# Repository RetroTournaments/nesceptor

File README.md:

# NESceptor

The NESceptor is a small hardware mod that adds a USB output to a 1985 Nintendo Entertainment System.
This mod is designed to provide support for speedrunning and speedrunning competitions.
The primary use case is to:

 - Allow for live RAM watch
 - Transmit console power status
 - Transmit precise timing information

## Design Decisions

### Why this overall design?

The console is to be treated with respect.
Although nearly [62 million units](https://en.wikipedia.org/wiki/Nintendo_Entertainment_System) were sold, they are no longer manufactured and should not be unnecessarily damaged.
The case (shell) of the Nintendo Entertainment system is _not_ to be cut or irreversibly modified.
The electronics are _not_ to be irreversibly modified.

To satisfy this requirement - while also balancing the desires to be able to quickly install a NESceptor - a two-part design was chosen.
The first board sits inside the console and attaches directly to the back of the CPU via a series of castellations.
This first board provides level translation and hosts the microcontroller which does all necessary i/o and processing.

The second part sits in the small outside slot on the back of the console and is attached via double sided tape and a small cable which goes back to the in console pcb.
This second board has ESD protection and the USB port for power in and data trasmission out.

A rough block diagram is below:

```
                     +--inconsole/--------------------+   +--usbport/---------+
     +------------+  |  +--------+    +------------+  |   |                   |
     |            |  |  |        |    |            |  |   | USB connection    |
     | NES CPU    |  |  | 5V to  |    | Rp2350     |  |   |                   |
     |            |  |  | 3.3V   |    | Micro-     |  |   | ESD protection    |
     | 8 data     |  |  |        |    | controller |  |   |                   |
     | 14 addr    | --> | Level  | -> |            | ---> |                   |
     | 3 aux      |  |  | Trans- |    | Watching / | <--- |                   |
     | --         |  |  | lators |    | Filtering  |  |   |                   |
     | 25 signals |  |  |        |    |            |  |   |                   |
     |            |  |  |        |    |            |  |   |                   |
     +------------+  |  +--------+    +------------+  |   |                   |
                     +--------------------------------+   +-------------------+ 
```

### Why Castellations?

The `inconsole` pcb is connected to the NES CPU with 40 castellations.
Consider:

- Removing the CPU and/or PPU can be difficult for novices (ahem) and requires patience, dedicated tools, and practice.
  Then once removed a socket is installed, and the CPU/PPU have to be installed into yet another socket, and the whole thing is fiddly and may lead to damage.
- The CPU itself is not subjected to heat or potential damage (when removing it), and is left basically alone with this design.
- A flex pcb was tried at one point, but it proved very difficult to install and remove.
  Flex pcbs are also more expensive to manufacture.

The main drawback to the castellations is that they may make the nesceptor difficult to remove, although this has not been tested yet.

### Which signals are needed from the console?

The following signals are absolutely required:

- Data lines 0 to 7 (8 total), these are self explanatory!
- Address lines 0 to 10 and 13-15 (14 total). Address lines 11 and 12 are not necessary because they are [unmapped](https://www.nesdev.org/wiki/CPU_memory_map).
- `NES_RST` when low the console is off, and that is important to know.
- `M2` is the clock
- `R/W` for read / write (low is write) 

This gives a total of 25 signals.

Historically `NMI` was also watched - but it was not used in the first version.
Maybe the controller pins are important, or `IRQ`, but they were never hooked up in the original.

### Notes on level translation

The NES is a 5V system, which is relatively high by modern standards, as most modern microcontrollers only have 3.3V tolerant inputs.
For example the [RP2350 datasheet](https://datasheets.raspberrypi.com/rp2350/rp2350-datasheet.pdf) indicates a maximum 3.63V supply voltage (`IOVDD`) and `IOVDD + 0.3` as maximum input voltage.
The NES signals must be translated to not damage the microcontrollers.

The level translators must not be used to change or interact with the console whatsoever.
They are preferably unidirectional.
This is imperative to maintain the legitimacy of the speedrunning and should be easily verified by third parties.

### Why the RP2350?

An earlier version of the NESceptor used an FPGA - specifically the Lattice iCE40 HX on the Alchitry CU development board, however:

- FPGAs are expensive.
- FPGAs are difficult to program (requiring some HDL).

The RP2350 is cheaper and should be capable of reading the NESs roughly 2 MHz signals:

- [This logic analyzer project](https://github.com/gusmanb/logicanalyzer/tree/master) uses a raspberry pi pico and boasts 100Msps
- And [this one](https://github.com/dotcypress/ula) also gets similar speeds.

### Why USB

USB is simple and well supported, people probably already have a ton of cables.
This will allow for communication and power delivery.
Ethernet is not necessary in this application because the nesbox mini pc will handle that, and would introduce some additional complications when it comes to networking.
Wifi for communication is expected to be unreliable - although this is unknown.

## Dev Instructions

### PCB Development

Install [KiCad](https://www.kicad.org/) for schematics / pcb design / etc.
I just use `snap install kicad`.
This got me `kicad 9.0.1` last time.
I'm using KiCad because it's free, and this is an open source project.

### Enclosure Development

Install [OpenSCAD](https://openscad.org/) for the 3d printed usbport enclosure.
I just use `snap install openscad`.
This got me `openscad 2021.01` last time.
I'm using OpenSCAD because its free, programmatic, and this is an open source project.

### Firmware Development

Firmware is developed using the [RP2350 C/C++ SDK](https://www.raspberrypi.com/documentation/microcontrollers/c_sdk.html).

To get started you need to have cloned this repo with submodules, or else use `git submodule update --init --recursive`.
Install the necessary prerequisites for the pico sdk:

```
sudo apt install cmake gcc-arm-none-eabi libnewlib-arm-none-eabi libstdc++-arm-none-eabi-newlib
```

Then you have to initialize the cmake build system with:

```
mkdir build
cd build
../scripts/cmake.sh
```

Then to build the firmware (source code in `include/` and `src/`), simply use `make`.

To flash the firmware to the nesceptor you need to hold the bootsel button when plugging it in, and then drag and rop the completed `.uf2` file onto the device.
It should then reboot and start running immediately.

### Ordering instructions

Under construction.

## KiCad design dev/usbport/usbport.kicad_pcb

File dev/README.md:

# Dev log

## 2025-10 `testbench/` Design

Round two developing nesceptor begins.
New thoughts:

  - Document more of the development process / decisions.
  - Order everything with PCB assembly.
    I am sick of debugging soldering issues.
    I also want to be able to order more easily - and not have to spend assembly time on my side.

Today I verified that my little TXU0104PWR breakout board worked.
Also, my original connector Molex 5051104091 is on the JLCPCB Parts library!

First item to design / order is a 5051104091 -> Digital discovery adapter that allows for exploration of the signals, and allows hooking up the pico 2 for initial development.
A sort of test bench hence the directory: `testbench/`.

- 5051104091, connector to get all 40 signals from the CPU
- To 5v -> 3.3v level translater prototype
    - TLV1117LV33DCYR for 5v to 3.3v (first test for this part)
    - TXU0104 translators (second implementation of this part)
- To pins with labels (all pins!?)

Review of the connector from my current breakout installed in several NESes

```
5051104091
                    |    |
                    |    |
              40            --  +5V
              39            ->  OUT0
              38            ->  OUT1
------------  37            ->  OUT2 
              36            ->  /OE1  
              35            ->  /OE2  
              34            ->  R/W   
              33            <-  /NMI  
              32            <-  /IRQ
              31            ->  M2
              30            <-  TST (usually GND)
              29            <-  CLK
              28            <>  D0
              27            <>  D1
              26            <>  D2 
              25            <>  D3 
              24            <>  D4 
              23            <>  D5 
              22            <>  D6
              21            <>  D7
 cable        20            --  GND
              19            ->  A15
              18            ->  A14 
              17            ->  A13  
              16            ->  A12   
              15            ->  A11    
              14            ->  A10     
              13            ->  A9      
              12            ->  A8       
              11            ->  A7        
              10            ->  A6         
               9            ->  A5          
               8            ->  A4           
               7            ->  A3            
               6            ->  A2             
               5            ->  A1              
------------   4            ->  A0               
               3            <-  RST
               2            ->  AD2
               1            ->  AD1
                    |    |
                    |    |
```

The rev 1 testbench has a little section for converting the NES 5v to 3.3v, and then some translators to get the signals into the digital discovery.
I ordered it, now to wait for it to show up.

The plan for when it does is to hook it up to the nes and the [Digital Discovery](https://digilent.com/shop/digital-discovery-portable-usb-logic-analyzer-and-digital-pattern-generator/).
This will allow me to document some of the timing information I will need when developing the inconsole firmware.
I have some earlier things kicking around - but they are not in keeping with the new repo structure and philosophy with documenting everything better.

## 2025-10 `inconsole/` -- rev 0

The next pcb I have designed and ordered is a 0th revision for the inconsole.
This is to see if I can fit all the parts, if I can design and order a working RP2350 board, and many other things.

Basically just following the RP2350 hardware design document, and shooting by the hip.
Going to try the RP2354A so I don't have to worry about fitting the flash on there.
I made an initial board which has all the level translation / power stuff contained within the necessary footprint of the NES CPU, and then some extra stuff on the outside for debugging and testing.
I ordered five of these with assembly and will try to learn as many lessons as possible from this.

First few things before it has even shown up.

- Sticking to 0402 components is helpful for assembly and keeping assembly costs down.
  I did 0201 for a bit, but then it was going to require more advanced assembly and higher costs.
- Ensure hole sizes are in tolerance.
- Include the pin 0 on silkscreen to avoid back and forth email.

Waiting for it to show up, and then will test!

## 2025-10 `usbport/` -- rev 0

Before even the other two revision 0s have shown up I'm investigating the `usbport/`.
Essentially I'm just going to steal the design from the [Unified Daughterboard](https://github.com/Unified-Daughterboard/UDB-S) project - which is another open source project primarily for mechanical keyboards.
Unfortunately their original design does not fit exactly where I want this to fit, so I will have to move things around a little bit probably screwing things up in the process.

One other main consideration about the usbport is that it needs a little enclosure to keep everything neat and tidy and protected.
I was originally thinking of coming out the left of the console - but we have power out the back, and composite out the right, so would be better to not add another cable out another side.
Then I ordered a unified daughterboard just to test, and the Pico EZMate connector is so small that it fits out the expansion port directly, and does not need to come out the vents.
Going to try for out the back on the 0th revision.

The back slot is about 99mm long, 12.5mm deep, ~16 mm wide (15.9 at 'top', 16.5 at 'bottom').
Let's imagine then 1.5mm thick walls on both sides, gives me a 12 mm wide pcb, 1.6mm thick.
I do not think I need to go the full length, but it would make it a bit easier for pushing the usb cable in to have some backing.
Regardless the PCB itself does not need to go to the back.

In keeping with stealing from the unified daughterboard project, we'll be using this [usb c connector - C165948](https://jlcpcb.com/partdetail/Korean_HropartsElec-TYPE_C_31_M12/C165948).

For the enclosure thinking of starting with a single hole in the middle M3 with [threaded inserts](https://www.mcmaster.com/products/threaded-inserts/threaded-inserts-3~/tapered-heat-set-inserts-for-plastic-7/).

## 2025-10 `inconsole/` -- rev 0 continued

The inconsole prototype showed up first and incredibly the RP2354a is actually working??
Just straight up plugged in the usb via a unified daughterboard (because my usbport rev is not done), and it just booted up with no problems..
Then I was able to install my own firmware - just a hello world thing, and it worked? Like uhhhhh. Insane!

> Rev 1 - Include the bootsel button within the final design. Actually no, the boot at 1200 baud does it.
> Rev 1 - Have not needed the run button or the debug port yet.

Now I need to test the 5V level translation part, and actually read the GPIO.
I wrote a small program (in this commit), and then just by shorting the RST pin to 5V with a little jumper cable it works.
No smoke either.
I just think everything is working?
We do have to get into the nitty gritty with timing and stuff now.
Hopefully testbench shows up - do I need to do some PIO stuff here?

## 2025-10 Wires
I ordered 200 25cm wires from [here](https://www.alibaba.com/product-detail/Customized-Molex-EZmate-78171-78172-1_1600697379284.html).
Hopefully long enough, and correct!

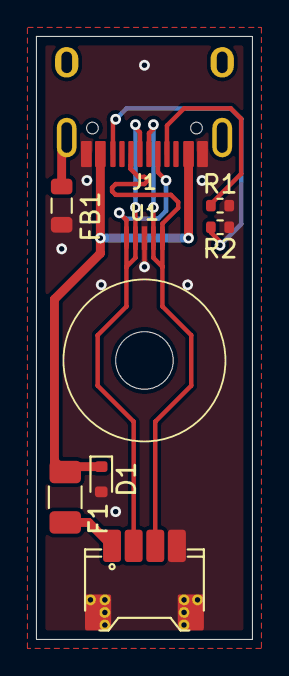
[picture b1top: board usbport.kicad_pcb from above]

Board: 2 copper layers, 12.0 x 33.5 mm, 9 parts (0 on the bottom side), 8 nets.

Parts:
D1: ESD5Z5V0; D_SOD-523
F1: SMD0805-050-16V; Fuse_1206_3216Metric
FB1: GZ2012D601TF; L_0805_2012Metric
H1: MountingHole; MountingHole_3.2mm_M3
J1: USB_C_Receptacle_USB2.0_16P; HRO-TYPE-C-31-M-12-Assembly
J2: Conn_01x04_MountingPin; PicoEZMate-Reinforced-Lite
R1, R2: 5.1k; R_0402_1005Metric
U1: TPD4E05U06DQAR; USON-10_2.5x1.0mm_P0.5mm

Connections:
+5V: F1.2, J2.1
D+: J1.A6 (D+), J1.B6 (D+), J2.3, U1.4 (D2+), U1.5 (D2-), U1.6 (NC), U1.7 (NC)
D-: J1.A7 (D-), J1.B7 (D-), J2.2, U1.1 (IO1), U1.2 (IO2), U1.9 (NC), U1.10 (NC)
GND: D1.2 (A2), FB1.2, J1.A1 (GND), J1.B1 (GND), J2.4, J2.MP (MountPin), R1.1, R2.2, U1.3 (GND), U1.8 (GND)
GNDPWR: FB1.1, J1.S1 (SHIELD)
unnamed: J1.A5 (CC1), R1.2
unnamed: J1.B5 (CC2), R2.1
VBUS: D1.1 (A1), F1.1, J1.A4 (VBUS), J1.B4 (VBUS)

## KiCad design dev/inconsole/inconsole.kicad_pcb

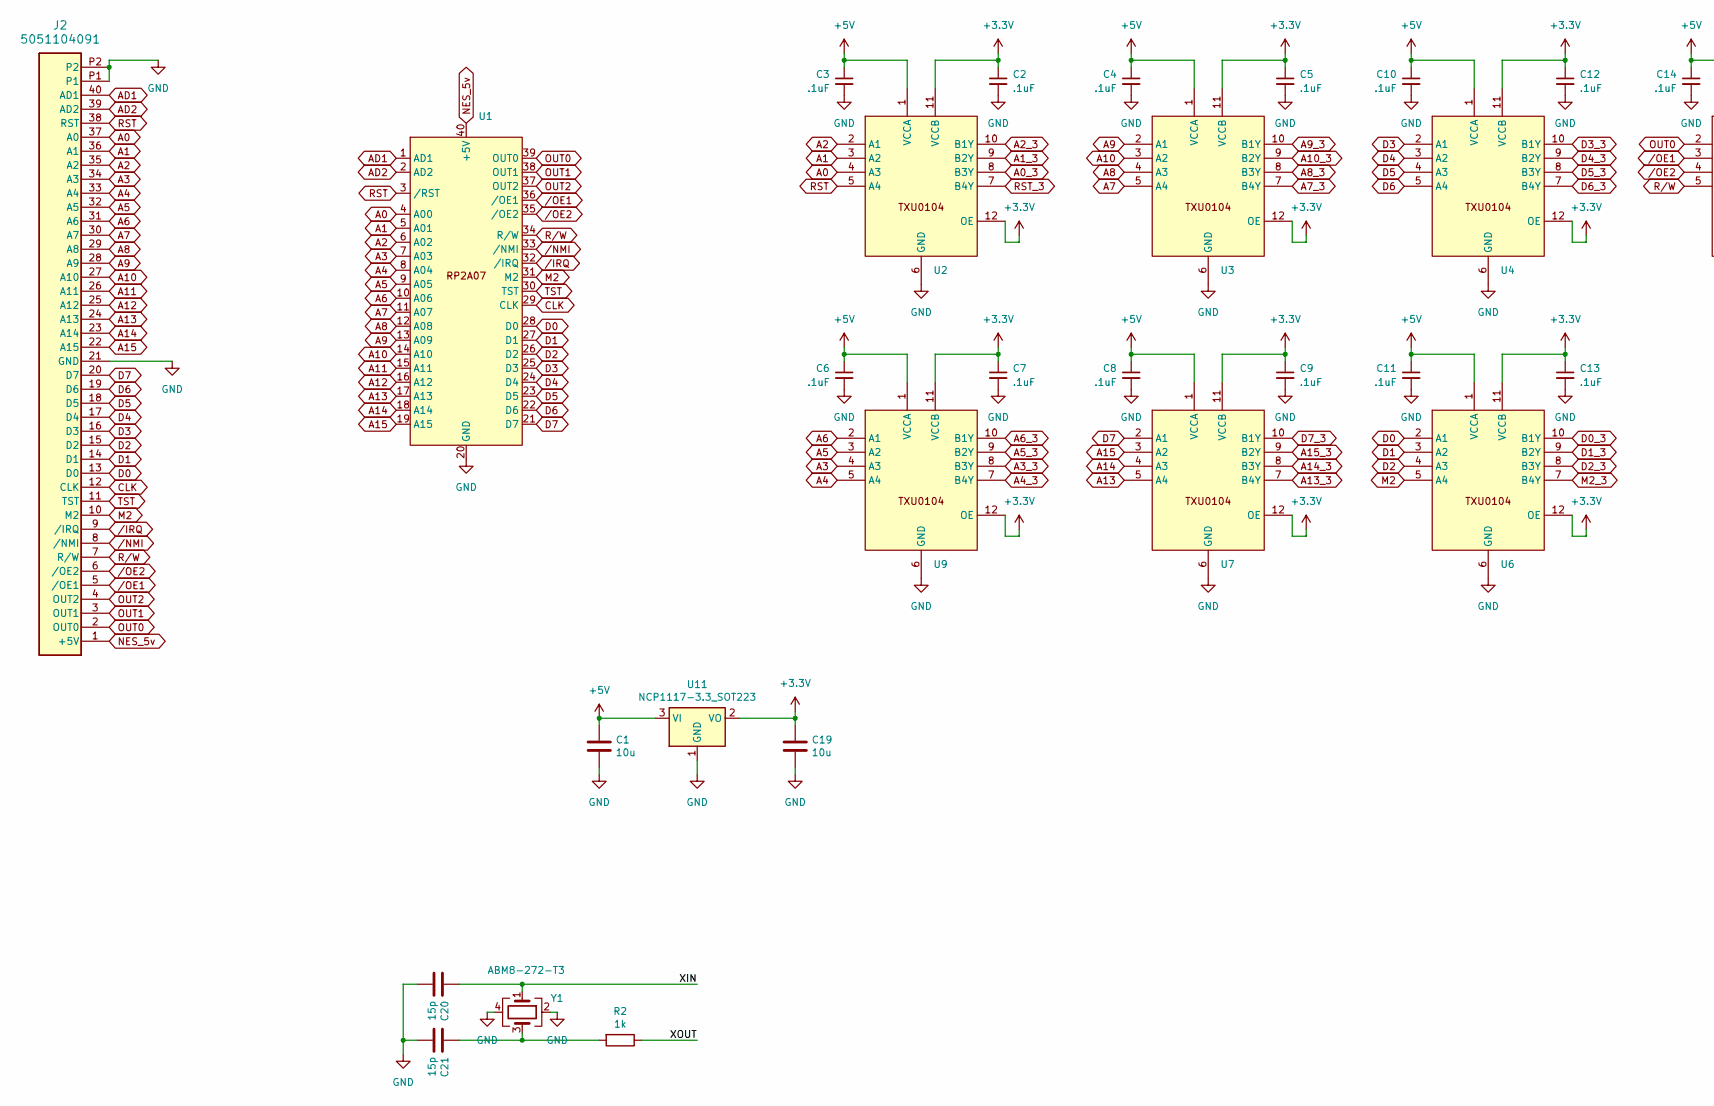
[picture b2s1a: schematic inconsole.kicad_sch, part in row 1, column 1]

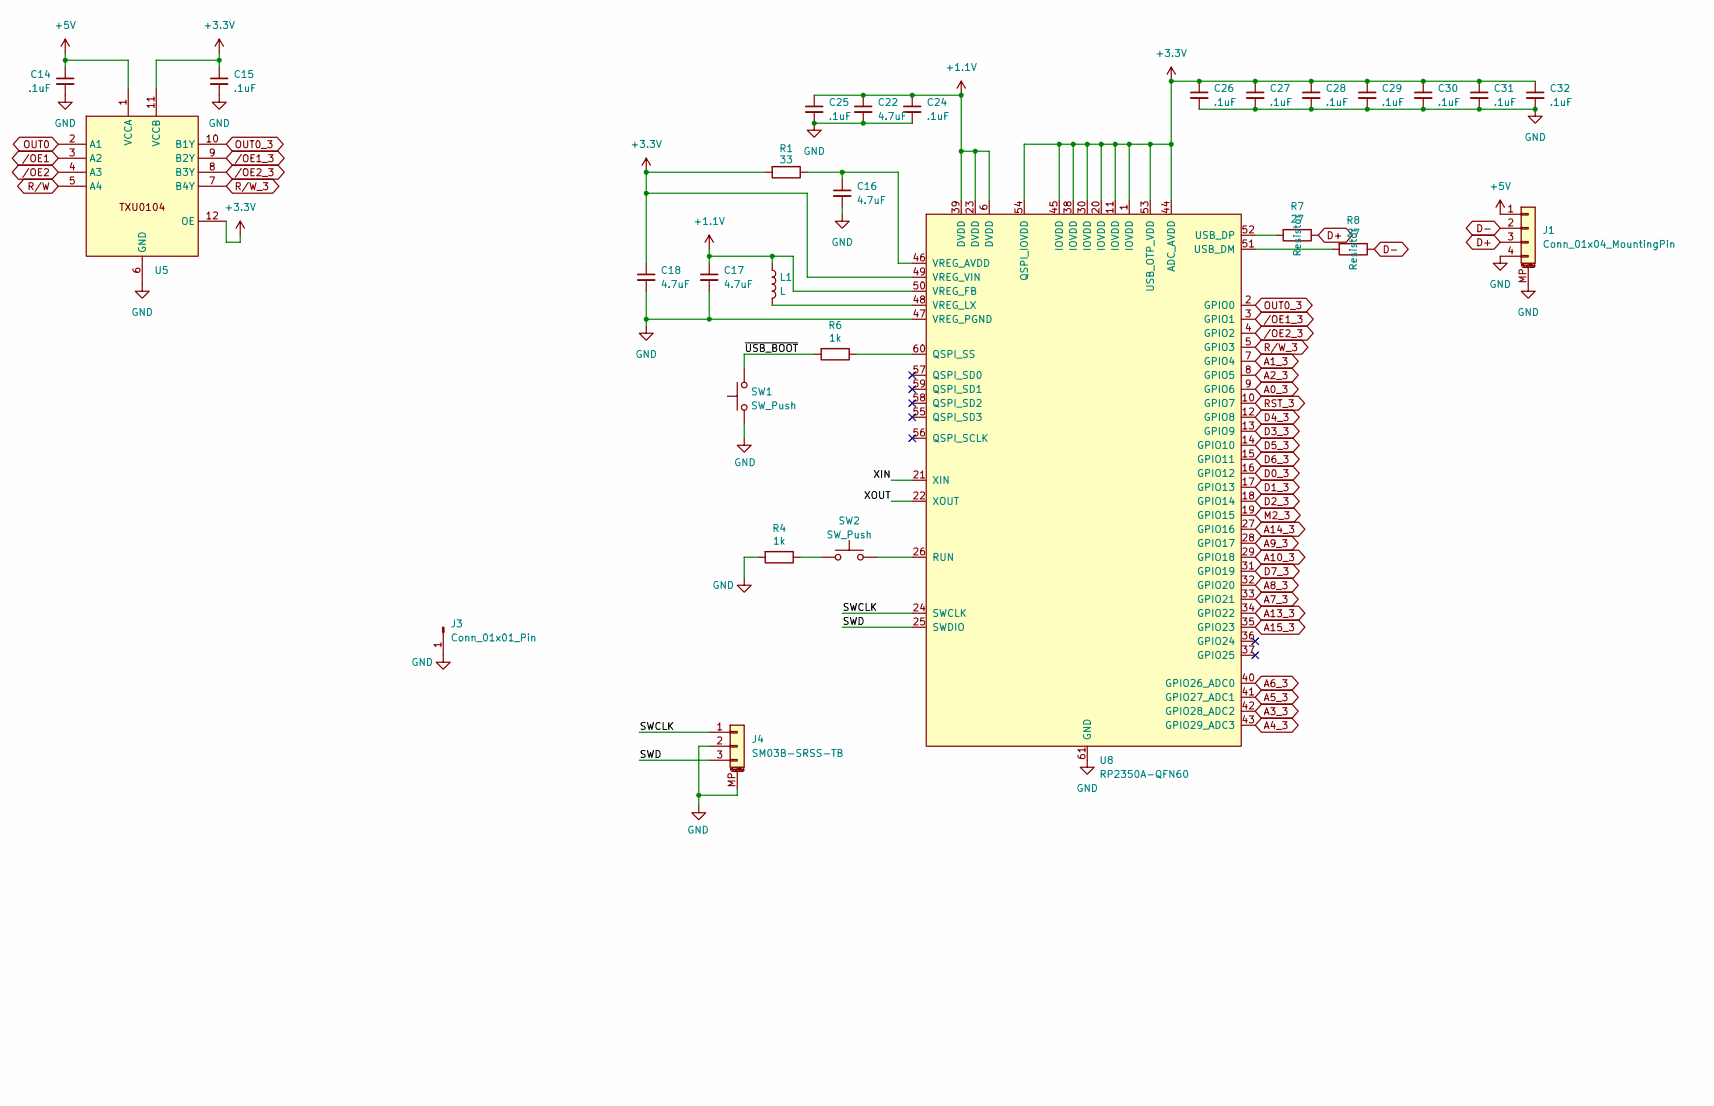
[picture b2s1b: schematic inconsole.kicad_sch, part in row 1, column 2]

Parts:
C1, C19: 10u; C_0805_2012Metric
C2, C3, C4, C5, C6, C7, C8, C9, C10, C11, C12, C13, C14, C15, C24, C25, C26, C27, C28, C29, C30, C31, C32: .1uF; C_0402_1005Metric
C16, C17, C18, C22: 4.7uF; C_0402_1005Metric
C20, C21: 15p; C_0402_1005Metric
J1: Conn_01x04_MountingPin; PicoEZMate-Reinforced-Lite; Manufacturer Part Number 78171-0004; LCSC Part Number C588524
J2: 5051104091; CON_5051104091_MOL
J3: Conn_01x01_Pin; PinSocket_1x01_P2.54mm_Vertical
J4: SM03B-SRSS-TB; JST_SH_SM03B-SRSS-TB_1x03-1MP_P1.00mm_Horizontal
L1: L; AOTA-B201610S3R3-101-T
R1: 33; C_0402_1005Metric
R2, R6: 1k; C_0402_1005Metric
R4: 1k; R_0402_1005Metric
R7, R8: 27; C_0402_1005Metric
SW1, SW2: SW_Push; TS-1088-AR02016
U1: RP2A07
U2, U3, U4, U5, U6, U7, U9: PQFP12_RUT_TEX
U8: RP2350A-QFN60; RP2350A_QFN-60_EP_7.75x7.75_Pitch0.4mm
U11: NCP1117-3.3_SOT223; SOT-223-3_TabPin2
Y1: ABM8-272-T3; Crystal_SMD_3225-4Pin_3.2x2.5mm

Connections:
+1.1V: C17.1, C22.1, C24.1, C25.1, L1.1, U8.6 (DVDD), U8.23 (DVDD), U8.39 (DVDD), U8.50 (VREG_FB)
+3.3V: C2.1, C5.1, C7.1, C9.1, C12.1, C13.1, C15.1, C18.1, C19.1, C26.1, C27.1, C28.1, C29.1, C30.1, C31.1, C32.1, R1.2, U2.11 (VCCB), U2.12 (OE), U3.11 (VCCB), U3.12 (OE), U4.11 (VCCB), U4.12 (OE), U5.11 (VCCB), U5.12 (OE), U6.11 (VCCB), U6.12 (OE), U7.11 (VCCB), U7.12 (OE), U8.1 (IOVDD), U8.11 (IOVDD), U8.20 (IOVDD), U8.30 (IOVDD), U8.38 (IOVDD), U8.44 (ADC_AVDD), U8.45 (IOVDD), U8.49 (VREG_VIN), U8.53 (USB_OTP_VDD), U8.54 (QSPI_IOVDD), U9.11 (VCCB), U9.12 (OE), U11.2 (VO)
+5V: C1.1, C3.1, C4.1, C6.1, C8.1, C10.1, C11.1, C14.1, J1.1, U2.1 (VCCA), U3.1 (VCCA), U4.1 (VCCA), U5.1 (VCCA), U6.1 (VCCA), U7.1 (VCCA), U9.1 (VCCA), U11.3 (VI)
/SWCLK: J4.1, U8.24 (SWCLK)
/SWD: J4.3, U8.25 (SWDIO)
/XIN: C20.1, U8.21 (XIN), Y1.1
/XOUT: R2.1, U8.22 (XOUT)
/~USB_BOOT: R6.2, SW1.2
A0: J2.37 (A0), U1.4 (A00), U2.4 (A3)
A0_3: U2.8 (B3Y), U8.9 (GPIO6)
A1: J2.36 (A1), U1.5 (A01), U2.3 (A2)
A1_3: U2.9 (B2Y), U8.7 (GPIO4)
A2: J2.35 (A2), U1.6 (A02), U2.2 (A1)
A2_3: U2.10 (B1Y), U8.8 (GPIO5)
A3: J2.34 (A3), U1.7 (A03), U9.4 (A3)
A3_3: U8.42 (GPIO28_ADC2), U9.8 (B3Y)
A4: J2.33 (A4), U1.8 (A04), U9.5 (A4)
A4_3: U8.43 (GPIO29_ADC3), U9.7 (B4Y)
A5: J2.32 (A5), U1.9 (A05), U9.3 (A2)
A5_3: U8.41 (GPIO27_ADC1), U9.9 (B2Y)
A6: J2.31 (A6), U1.10 (A06), U9.2 (A1)
A6_3: U8.40 (GPIO26_ADC0), U9.10 (B1Y)
A7: J2.30 (A7), U1.11 (A07), U3.5 (A4)
A7_3: U3.7 (B4Y), U8.33 (GPIO21)
A8: J2.29 (A8), U1.12 (A08), U3.4 (A3)
A8_3: U3.8 (B3Y), U8.32 (GPIO20)
A9: J2.28 (A9), U1.13 (A09), U3.2 (A1)
A9_3: U3.10 (B1Y), U8.28 (GPIO17)
A10: J2.27 (A10), U1.14 (A10), U3.3 (A2)
A10_3: U3.9 (B2Y), U8.29 (GPIO18)
A11: J2.26 (A11), U1.15 (A11)
A12: J2.25 (A12), U1.16 (A12)
A13: J2.24 (A13), U1.17 (A13), U7.5 (A4)
A13_3: U7.7 (B4Y), U8.34 (GPIO22)
A14: J2.23 (A14), U1.18 (A14), U7.4 (A3)
A14_3: U7.8 (B3Y), U8.27 (GPIO16)
A15: J2.22 (A15), U1.19 (A15), U7.3 (A2)
A15_3: U7.9 (B2Y), U8.35 (GPIO23)
AD1: J2.40 (AD1), U1.1 (AD1)
AD2: J2.39 (AD2), U1.2 (AD2)
CLK: J2.12 (CLK), U1.29 (CLK)
D0: J2.13 (D0), U1.28 (D0), U6.2 (A1)
D0_3: U6.10 (B1Y), U8.16 (GPIO12)
D1: J2.14 (D1), U1.27 (D1), U6.3 (A2)
D1_3: U6.9 (B2Y), U8.17 (GPIO13)
D2: J2.15 (D2), U1.26 (D2), U6.4 (A3)
D2_3: U6.8 (B3Y), U8.18 (GPIO14)
D3: J2.16 (D3), U1.25 (D3), U4.2 (A1)
D3_3: U4.10 (B1Y), U8.13 (GPIO9)
D4: J2.17 (D4), U1.24 (D4), U4.3 (A2)
D4_3: U4.9 (B2Y), U8.12 (GPIO8)
D5: J2.18 (D5), U1.23 (D5), U4.4 (A3)
D5_3: U4.8 (B3Y), U8.14 (GPIO10)
D6: J2.19 (D6), U1.22 (D6), U4.5 (A4)
D6_3: U4.7 (B4Y), U8.15 (GPIO11)
D7: J2.20 (D7), U1.21 (D7), U7.2 (A1)
D7_3: U7.10 (B1Y), U8.31 (GPIO19)
D+: J1.3, R7.1
D-: J1.2, R8.1
GND: C1.2, C2.2, C3.2, C4.2, C5.2, C6.2, C7.2, C8.2, C9.2, C10.2, C11.2, C12.2, C13.2, C14.2, C15.2, C16.2, C17.2, C18.2, C19.2, C20.2, C21.2, C22.2, C24.2, C25.2, C26.2, C27.2, C28.2, C29.2, C30.2, C31.2, C32.2, J1.4, J1.MP (MountPin), J2.21 (GND), J2.P1, J2.P2, J3.1, J4.2, J4.MP (MountPin), R4.2, SW1.1, U1.20 (GND), U2.6 (GND), U3.6 (GND), U4.6 (GND), U5.6 (GND), U6.6 (GND), U7.6 (GND), U8.47 (VREG_PGND), U8.61 (GND), U9.6 (GND), U11.1 (GND), Y1.2, Y1.4
M2: J2.10 (M2), U1.31 (M2), U6.5 (A4)
M2_3: U6.7 (B4Y), U8.19 (GPIO15)
NES_5v: J2.1 (+5V), U1.40 (+5V)
unnamed: C21.1, R2.2, Y1.3
unnamed: R4.1, SW2.1
unnamed: R6.1, U8.60 (QSPI_SS)
unnamed: SW2.2, U8.26 (RUN)
unnamed: R8.2, U8.51 (USB_DM)
unnamed: R7.2, U8.52 (USB_DP)
unnamed: C16.1, R1.1, U8.46 (VREG_AVDD)
unnamed: L1.2, U8.48 (VREG_LX)
OUT0: J2.2 (OUT0), U1.39 (OUT0), U5.2 (A1)
OUT0_3: U5.10 (B1Y), U8.2 (GPIO0)
OUT1: J2.3 (OUT1), U1.38 (OUT1)
OUT2: J2.4 (OUT2), U1.37 (OUT2)
RST: J2.38 (RST), U1.3 (/RST), U2.5 (A4)
RST_3: U2.7 (B4Y), U8.10 (GPIO7)
R/W: J2.7 (R/W), U1.34 (R/W), U5.5 (A4)
R/W_3: U5.7 (B4Y), U8.5 (GPIO3)
TST: J2.11 (TST), U1.30 (TST)
/IRQ: J2.9 (/IRQ), U1.32 (/IRQ)
/NMI: J2.8 (/NMI), U1.33 (/NMI)
/OE1: J2.5 (/OE1), U1.36 (/OE1), U5.3 (A2)
/OE1_3: U5.9 (B2Y), U8.3 (GPIO1)
/OE2: J2.6 (/OE2), U1.35 (/OE2), U5.4 (A3)
/OE2_3: U5.8 (B3Y), U8.4 (GPIO2)

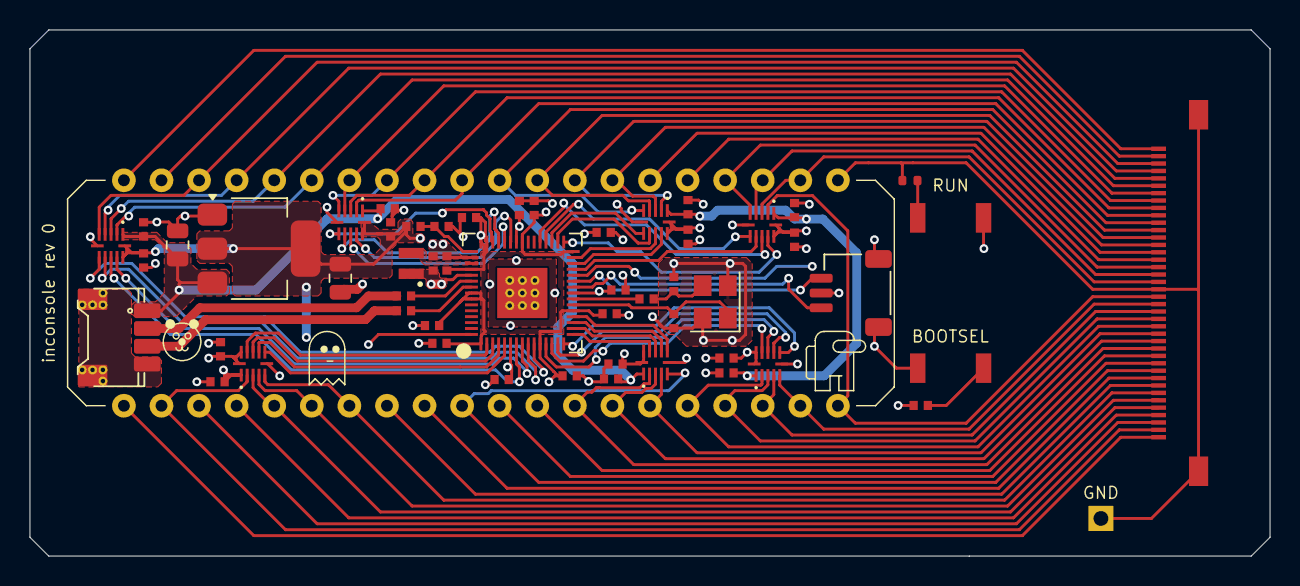
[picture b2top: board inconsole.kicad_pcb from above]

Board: 4 copper layers, 83.8 x 35.6 mm, 55 parts (1 on the bottom side), 86 nets.

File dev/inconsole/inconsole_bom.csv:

Comment,Designator,Footprint,LCSC Part Number
10u,"C1,C19",C_0805,C15850
.1uF,"C2,C3,C4,C5,C6,C7,C8,C9,C10,C11,C12,C13,C14,C15,C24,C25,C26,C27,C28,C29,C30,C31,C32",C_0402,C1525
4.7uF,"C16,C17,C18,C22",C_0402,C76995
15p,"C20,C21",C_0402,C1548
Conn_01x04_MountingPin,J1,PicoEZMate,C588524
5051104091,J2,5051104091,C588009
SM03B-SRSS-TB,J4,SMD,C160403
AOTA-B201610S3R3-101-T ,L1,L_0806,C42411119
33R,R1,R_0402,C25105
1k,"R2,R4,R6",R_0402,C11702
27R,"R7,R8",R_0402,C25100
SW_Push,"SW1,SW2",SMD4x3mm,C720477
TXU0104RUTR,"U2,U3,U4,U5,U6,U7,U9",UQFN-12(1.7x2),C5187176
RP2354A,U8,QFN-60(7x7),C41378174
NCP1117ST33T3G,U11,SOT-223,C26537
ABM8-272-T3,Y1,SMD3225-4P,C20625731

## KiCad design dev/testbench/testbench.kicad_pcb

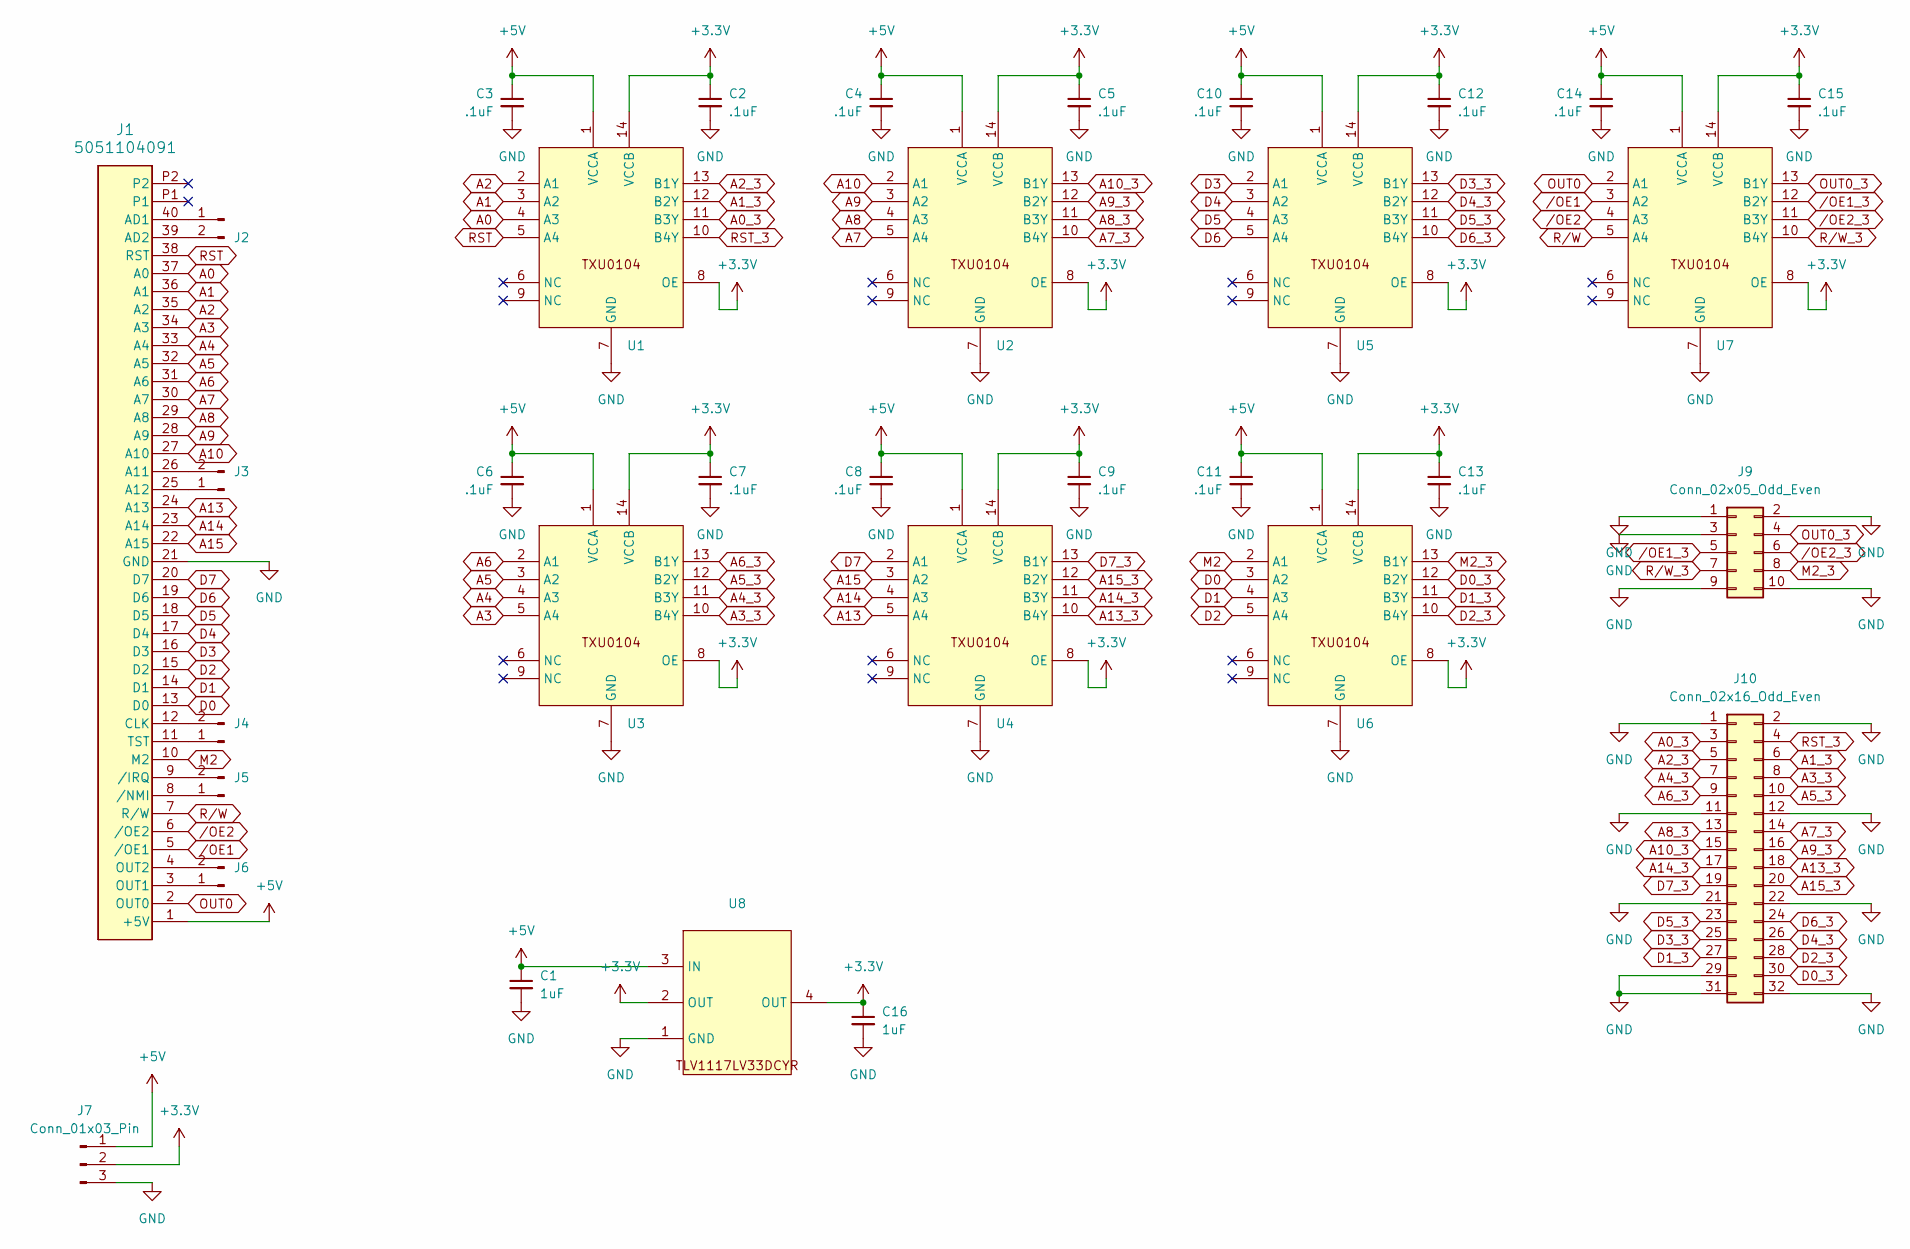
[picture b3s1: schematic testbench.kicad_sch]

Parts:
C1, C16: 1uF; C_0805_2012Metric
C2, C3, C4, C5, C6, C7, C8, C9, C10, C11, C12, C13, C14, C15: .1uF; C_0402_1005Metric
J1: 5051104091; CON_5051104091_MOL
J2, J3, J4, J5, J6: Conn_01x02_Pin; PinHeader_1x02_P2.54mm_Vertical
J7: Conn_01x03_Pin; PinHeader_1x03_P2.54mm_Vertical
J9: Conn_02x05_Odd_Even; PinHeader_2x05_P2.54mm_Vertical
J10: Conn_02x16_Odd_Even; PinHeader_2x16_P2.54mm_Vertical
U1, U2, U3, U4, U5, U6, U7: DHVQFN-14-1EP_2.5x3mm_P0.5mm_EP1x1.5mm
U8: SOT-223

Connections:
+3.3V: C2.1, C5.1, C7.1, C9.1, C12.1, C13.1, C15.1, C16.1, J7.2, U1.8 (OE), U1.14 (VCCB), U2.8 (OE), U2.14 (VCCB), U3.8 (OE), U3.14 (VCCB), U4.8 (OE), U4.14 (VCCB), U5.8 (OE), U5.14 (VCCB), U6.8 (OE), U6.14 (VCCB), U7.8 (OE), U7.14 (VCCB), U8.2 (OUT), U8.4 (OUT)
+5V: C1.1, C3.1, C4.1, C6.1, C8.1, C10.1, C11.1, C14.1, J1.1 (+5V), J7.1, U1.1 (VCCA), U2.1 (VCCA), U3.1 (VCCA), U4.1 (VCCA), U5.1 (VCCA), U6.1 (VCCA), U7.1 (VCCA), U8.3 (IN)
A0: J1.37 (A0), U1.4 (A3)
A0_3: J10.3, U1.11 (B3Y)
A1: J1.36 (A1), U1.3 (A2)
A1_3: J10.6, U1.12 (B2Y)
A2: J1.35 (A2), U1.2 (A1)
A2_3: J10.5, U1.13 (B1Y)
A3: J1.34 (A3), U3.5 (A4)
A3_3: J10.8, U3.10 (B4Y)
A4: J1.33 (A4), U3.4 (A3)
A4_3: J10.7, U3.11 (B3Y)
A5: J1.32 (A5), U3.3 (A2)
A5_3: J10.10, U3.12 (B2Y)
A6: J1.31 (A6), U3.2 (A1)
A6_3: J10.9, U3.13 (B1Y)
A7: J1.30 (A7), U2.5 (A4)
A7_3: J10.14, U2.10 (B4Y)
A8: J1.29 (A8), U2.4 (A3)
A8_3: J10.13, U2.11 (B3Y)
A9: J1.28 (A9), U2.3 (A2)
A9_3: J10.16, U2.12 (B2Y)
A10: J1.27 (A10), U2.2 (A1)
A10_3: J10.15, U2.13 (B1Y)
A13: J1.24 (A13), U4.5 (A4)
A13_3: J10.18, U4.10 (B4Y)
A14: J1.23 (A14), U4.4 (A3)
A14_3: J10.17, U4.11 (B3Y)
A15: J1.22 (A15), U4.3 (A2)
A15_3: J10.20, U4.12 (B2Y)
D0: J1.13 (D0), U6.3 (A2)
D0_3: J10.30, U6.12 (B2Y)
D1: J1.14 (D1), U6.4 (A3)
D1_3: J10.27, U6.11 (B3Y)
D2: J1.15 (D2), U6.5 (A4)
D2_3: J10.28, U6.10 (B4Y)
D3: J1.16 (D3), U5.2 (A1)
D3_3: J10.25, U5.13 (B1Y)
D4: J1.17 (D4), U5.3 (A2)
D4_3: J10.26, U5.12 (B2Y)
D5: J1.18 (D5), U5.4 (A3)
D5_3: J10.23, U5.11 (B3Y)
D6: J1.19 (D6), U5.5 (A4)
D6_3: J10.24, U5.10 (B4Y)
D7: J1.20 (D7), U4.2 (A1)
D7_3: J10.19, U4.13 (B1Y)
GND: C1.2, C2.2, C3.2, C4.2, C5.2, C6.2, C7.2, C8.2, C9.2, C10.2, C11.2, C12.2, C13.2, C14.2, C15.2, C16.2, J1.21 (GND), J7.3, J9.1, J9.2, J9.3, J9.9, J9.10, J10.1, J10.2, J10.11, J10.12, J10.21, J10.22, J10.29, J10.31, J10.32, U1.7 (GND), U2.7 (GND), U3.7 (GND), U4.7 (GND), U5.7 (GND), U6.7 (GND), U7.7 (GND), U8.1 (GND)
M2: J1.10 (M2), U6.2 (A1)
M2_3: J9.8, U6.13 (B1Y)
unnamed: J1.26 (A11), J3.2
unnamed: J1.25 (A12), J3.1
unnamed: J1.40 (AD1), J2.1
unnamed: J1.39 (AD2), J2.2
unnamed: J1.12 (CLK), J4.2
unnamed: J1.3 (OUT1), J6.1
unnamed: J1.4 (OUT2), J6.2
unnamed: J1.11 (TST), J4.1
unnamed: J1.9 (/IRQ), J5.2
unnamed: J1.8 (/NMI), J5.1
OUT0: J1.2 (OUT0), U7.2 (A1)
OUT0_3: J9.4, U7.13 (B1Y)
RST: J1.38 (RST), U1.5 (A4)
RST_3: J10.4, U1.10 (B4Y)
R/W: J1.7 (R/W), U7.5 (A4)
R/W_3: J9.7, U7.10 (B4Y)
/OE1: J1.5 (/OE1), U7.3 (A2)
/OE1_3: J9.5, U7.12 (B2Y)
/OE2: J1.6 (/OE2), U7.4 (A3)
/OE2_3: J9.6, U7.11 (B3Y)

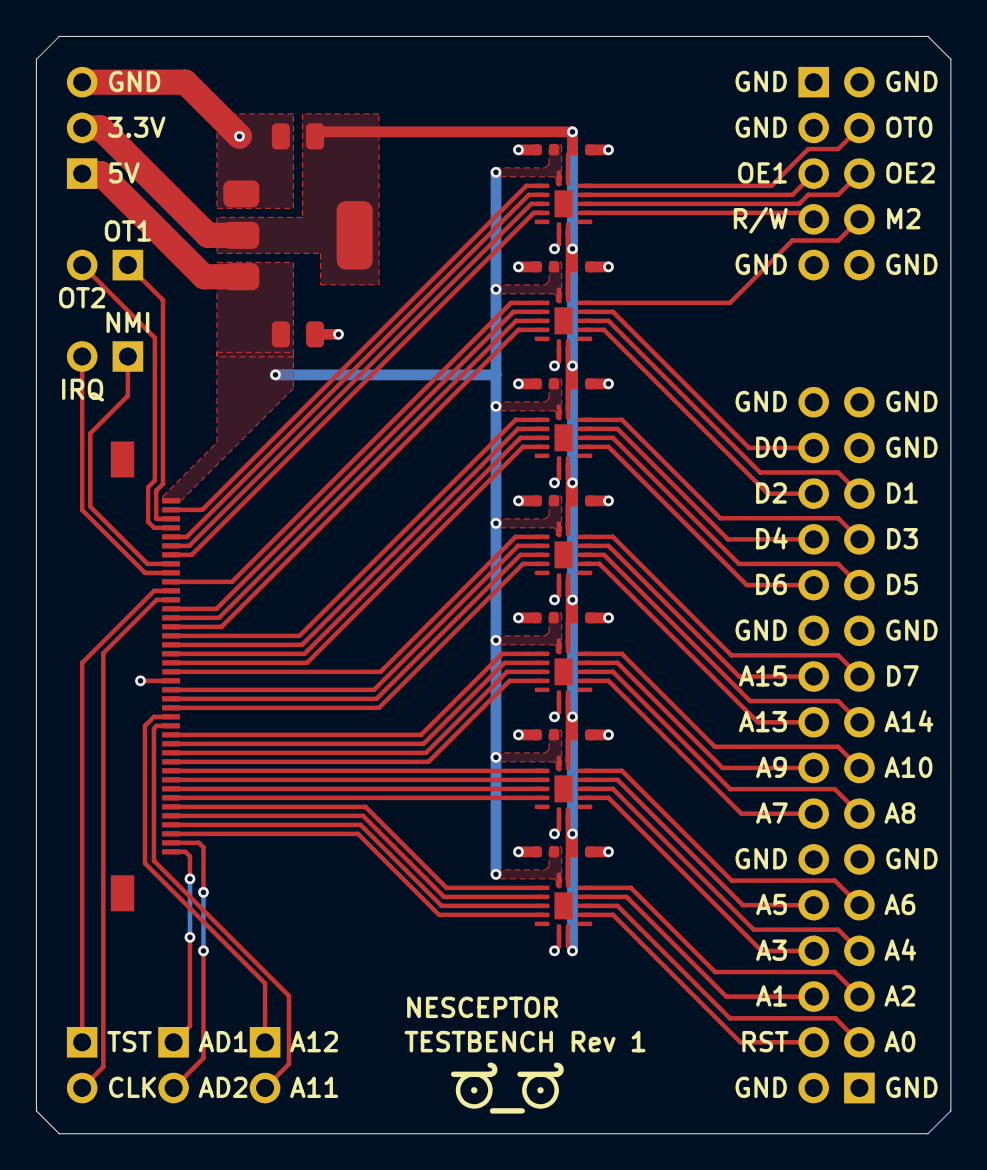
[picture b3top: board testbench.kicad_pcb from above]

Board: 2 copper layers, 50.8 x 61.0 mm, 33 parts (0 on the bottom side), 69 nets.

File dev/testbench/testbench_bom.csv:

Comment,Designator,Footprint,LCSC Part Number
"1uF","C1,C16",0805,C1712
".1uF","C2,C3,C4,C5,C6,C7,C8,C9,C10,C11,C12,C13,C14,C15",0402,C1525
"5051104091",J1,5051104091,C588009
"TXU0104BQAR","U1,U2,U3,U4,U5,U6,U7",WQFN-14,C4354911
"TLV1117LV33DCYR",U8,SOT-223,C15578

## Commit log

2024-05-09 Add initial README file
2024-05-09 Add initial datasheets via git-lfs
2024-05-09 Add the pico-sdk submodule
2024-05-09 Add initial altium project
2024-05-09 Add old prototype
2025-01-18 Add old firmware
2025-10-06 Remove pico-sdk for now
2025-10-06 Update readme with minor thoughts / changes
2025-10-06 Add some more datasheets
2025-10-09 Add TLV1117LV datasheet
    I am trying this component to get a 3.3v supply for the level
    translation.
2025-10-09 Add the nesceptor kicad library for components
2025-10-09 Add the 'testbench' dev board to help develop the next major revision
    This board should help with hooking up a current NES to the logic
    analyzer and documenting those next steps. I'm sure it's silly but I
    haven't reviewed this one with a real engineer. Should show up in a few
    weeks!
2025-10-19 Add additional symbols to library
2025-10-19 Add initial inconsole rev 0
2025-10-19 Add missing BOM and Centroids from testbench
2025-10-21 Add an initial 3D printed enclosure for the usbport pcb
    Still need to investigate thickness in a few spots - and then need to
    get it printed and see about the threaded inserts / screws etc.
2025-10-21 Add an initial usbport design based on unified daughterboards
    This is still in progress, but will be the little piece that fits
    between the main inconsole board and the outside world. Thankfully can
    steal all the good ideas from the unified daughterboard project!
2025-10-21 Remove altium files, as no longer used
2025-10-21 Add initial firmware wiring, and a hello usb example
2025-10-27 Add initial usbport rev 0 - from the unified daughterboard project
